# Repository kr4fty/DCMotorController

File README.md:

# DCMotorController

Control de lazo cerrado para motores DC utilizando un ATMEGA328p (corazón del
  Arduino UNO) y un puente H tipo L293.

<!-- TOC depthFrom:1 depthTo:6 withLinks:1 updateOnSave:1 orderedList:0 -->

- [DCMotorController](#dcmotorcontroller)
	- [Descripción](#descripcin)
	- [Funcionamiento](#funcionamiento)
		- [Parámetros PID](#parmetros-pid)
	- [Características:](#caractersticas)
	- [Firmware](#firmware)
		- [Dependencias](#dependencias)
	- [Hardware](#hardware)
		- [Esquematico](#esquematico)
	- [Video](#video)
	- [Motores de corriente continua](#motores-de-corriente-continua)
		- [Ventajas de los Motores DC frente a los PaP](#ventajas-de-los-motores-dc-frente-a-los-pap)
		- [Desventajas de los Motores DC frente a los PaP](#desventajas-de-los-motores-dc-frente-a-los-pap)
	- [Proyectos Similares](#proyectos-similares)
	- [Licencia](#licencia)
	- [Autor](#autor)

<!-- /TOC -->

## Descripción
Este es una pequeña implementación de la librería [ArduinoPID](https://github.com/br3ttb/Arduino-PID-Library), para el control
de motores de corriente continua, DC, que cuenten con un encoder acoplado a su
eje.

Cuenta con soporte para **uno** o **dos** motores, dependiendo de como este
configurado dentro de _**motor.h**_.

La idea principal del proyecto es la de utilizar MOTORES DC/Servos en proyectos
de construcción de CNC en lugar de los tradicionales Motores Paso a Paso (PaP).

El sistema es compatible a nivel de pins de control, con los driver para motores
PaP, **STEP** y **DIR**, como por ejemplo el [Pololu A4988](https://www.pololu.com/product/1182).

## Funcionamiento
Un Arduino cargado con **GRBL**, por ejemplo, envía un pulso a través del pin **STEP**. Cada pulso que recibe el driver le dice al motor que tiene que avanzar un micropaso.

Luego por medio del pin **DIR** obtenemos la dirección de avance, si queremos ir en el sentido de las agujas del reloj, o al contrario.

De esta forma, cada vez que el driver recibe un pulso en el pin **STEP**, el circuito comprueba el estado del pin **DIR**, y alimenta las bobinas del motor en el orden adecuado.

### Parámetros PID
El proceso de sintonizado del PID se hizo de forma experimental, prueba/error, tratando de tener tanto el **overshoot** como el **tiempo de establecimiento** los mas chicos posibles.
Se llego a la conclusión que para el par de motores utilizados, los parámetros que mejor se ajustaban fueron los siguientes:

  * Setpoint > 50: </br>
      Kp = 10 // Agresive Kp</br>
      Ki = 1 // Agresive Ki</br>
      Kd = 0.01 // Agresive Kd</br>

  * Setpoint =< 50:</br>
      Kp = 5  // Conservative Kp</br>
      Ki = 0.1  // Conservative Ki</br>
      Kd = 0.001  // Conservative Kd</br>

Dependiendo del tipo de Motor/Servo utilizados, estos parámetros deberán ser cambiados. Esto ultimo se realizara modificando los prarametros AGGKp,AGGKi, AGGKd, CONSKp, CONSKi y CONSKd, dentro de **motor.h**

## Características:
  * El conjunto Driver-Servo/Motor remplaza al conjunto Driver-Motor/PaP
  * El corazón del sistema es un chip **ATMEGA328p**
  * Se puede controlar uno o dos motores simultáneamente
  * El Driver tiene cuatro señales de control: **DIR**, **STEP**, **ENABLE** y **RESET**
  * Cada motor puede ser controlado de forma independiente por medio de **DIR** y
    **STEP**
  * El sistema de control esta basado en un sistema PID
  * El PWM trabaja a una frecuencia de 31.25KHz, imperceptible al oído humano
  * Cuenta con un salida por puerto serie para depuración
  * Tanto las señales de entrada de los STEPs como las de los encoders, utilizan
    interrupciones del tipo **PIN CHANGE** (PCI)
  * El diseño del **PCB** fue realizado en [KiCAD](https://github.com/KiCad/)
  * La etapa de potencia de los motores fue realizada con un **puente H** del tipo L293D

## Firmware
### Dependencias
El proyecto depende de cuatro librerías:
  * [ArduinoPID](https://github.com/br3ttb/Arduino-PID-Library): Librería principal con la que se realiza el control de lazo
    cerrado
  * [EnableInterrupt](https://github.com/GreyGnome/EnableInterrupt): Encargada de vincular las interrupciones del tipo Pin-change con la respectiva ISR.
  * [EncoderPCI](https://github.com/kr4fty/EncoderPCI): Librería encargada de manejar los Encoders
  * [DCMotorServoPCI](https://github.com/kr4fty/DCMotorServoPCI): Es la librería en si, que realiza la gestión y el control del
    motor dc

## Hardware
Pins utilizados:

<table>
	<tr><th></th><th> Motor 1 </th></tr>
	<tr><th> <b>Arduino Pin</b> </th><th> <b>Descripción</b> </th></tr>
	<tr><td>10 </td><td> pwmX, chip enable 1 del L293D </td></tr>
	<tr><td>6  </td><td> in1X, salida hacia el pin 2, IN1, del L293D </td></tr>
	<tr><td>5  </td><td> in2X, salida hacia el pin 7, IN2, del L293D </td></tr>
	<tr><td>A2 </td><td> inAX, entrada A desde el encoder </td></tr>
	<tr><td>A3 </td><td> inBX, entrada B desde el encoder </td></tr>
	<tr><td>2  </td><td> stepX, entrada STEP proveniente del otro Arduino cargado con GRBL </td></tr>
	<tr><td>12 </td><td> dirX, entrada DIR proveniente del otro Arduino cargado con GRBL </td></tr>
</table>

<table>
	<tr><th></th><th> Motor 2 </th></tr>
	<tr><th> <b>Arduino Pin</b> </th><th> <b>Descripción</b> </th></tr>
	<tr><td> 11 </td><td> pwmY, chip enable 2 del L293D </td></tr>
	<tr><td> 8 </td><td> in1Y, salida hacia el pin 10, IN3, del L293D </td></tr>
	<tr><td> 9 </td><td> in2Y, salida hacia el pin 15, IN4, del L293D </td></tr>
	<tr><td> A0 </td><td> inAY, entrada A desde el encoder </td></tr>
	<tr><td> A1 </td><td> inBY, entrada B desde el encoder </td></tr>
	<tr><td> 3 </td><td> stepY, entrada STEP </td></tr>
	<tr><td> 13 </td><td> dirY, entrada DIR </td></tr>
</table>

<table>
	<tr><th></th><th> Global </th></tr>
	<tr><th> <b>Arduino Pin</b> </th><th> <b>Descripción</b> </th></tr>
	<tr><td> A5 </td><td> entrada ENABLE </td></tr>
	<tr><td> Rst </td><td> Reset del driver </td></tr>
</table>

### Esquematico

<p align="center">
  <br><br>
  <b>Circuito</b><br>
  
  <br>
</p>

## Video
<p align="center">
  <b>YouTube</b><br>
  
</p>

## Motores de corriente continua

### Ventajas de los Motores DC frente a los PaP
  * Poseen gran velocidad de giro
  * Alta aceleración/Par inicial
  * Son silenciosos
  * Movimiento suave y sin saltos
  * Control medianamente sencilla
  * Electrónica mas sencilla
  * Utiliza realimentación para el control del sistema
  * Debido a este ultimo, tiene alta precisión en posición (depende fuertemente
    del encoder acoplado)

### Desventajas de los Motores DC frente a los PaP
  * La potencia de funcionamiento pico sólo se desarrolla a altas velocidades
  * Debido a sus altas velocidades estos pueden calentarse mas rápidamente
    (podría necesitar un sistemas de ventilación)
  * Inercia mas elevada (depende de la  velocidad y la carga acoplada al eje)

## Proyectos Similares
  * [ServoStrap](https://github.com/danithebest91/ServoStrap) por _danithebest91_
  * [SuryaProCell-CNC](https://github.com/suryaprocell/SuryaProCell-CNC) por _suryaprocell_
  * [DC-Servo-Controller](https://github.com/makerbot/DC-Servo-Controller) por _makerbot_
  * [dcservo](https://github.com/misan/dcservo) por _misan_

## Licencia

GPLv2

## Autor

Tapia Favio

## Feedback

Por favor agradecería que me envies cualquier duda y/o comentario para mejorar el proyecto, gracias.

Mail: technicc (at) gmail.com

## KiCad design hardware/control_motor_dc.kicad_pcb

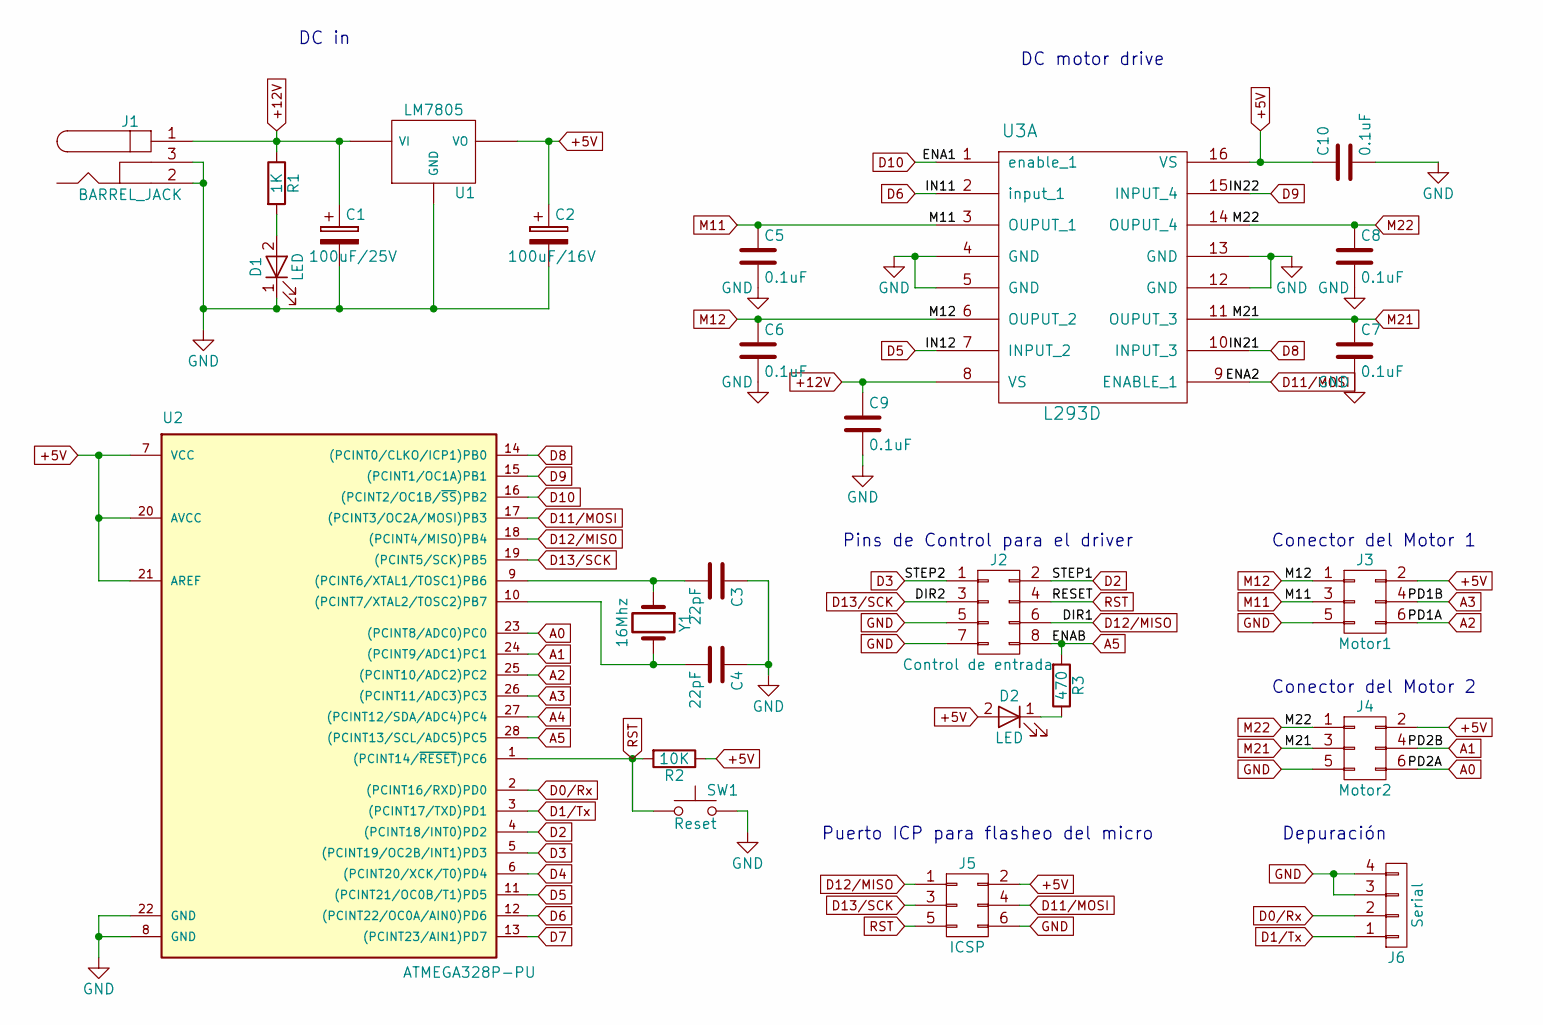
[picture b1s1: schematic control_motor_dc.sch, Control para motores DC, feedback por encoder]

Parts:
C1: 100uF/25V; CP_Radial_D5.0mm_P2.50mm
C2: 100uF/16V; CP_Radial_D5.0mm_P2.00mm
C3, C4: 22pF; C_Disc_D3.8mm_W2.6mm_P2.50mm
C5, C6, C7, C8, C9, C10: 0.1uF; C_Disc_D3.8mm_W2.6mm_P2.50mm
D1, D2: LED; LED_D3.0mm
J1: BARREL_JACK; JACK_ALIM
J2: Control de entrada; Socket_Strip_Straight_2x04_Pitch2.54mm
J3: Motor1; Socket_Strip_Straight_2x03_Pitch2.54mm
J4: Motor2; Socket_Strip_Straight_2x03_Pitch2.54mm
J5: ICSP; Pin_Header_Straight_2x03_Pitch2.54mm
J6: Serial; Pin_Header_Straight_1x04_Pitch2.54mm
R1: 1K; R_Axial_DIN0207_L6.3mm_D2.5mm_P2.54mm_Vertical
R2: 10K; R_Axial_DIN0207_L6.3mm_D2.5mm_P7.62mm_Horizontal
R3: 470; R_Axial_DIN0204_L3.6mm_D1.6mm_P7.62mm_Horizontal
SW1: Reset; SW_PUSH_6mm
U1: LM7805; TO-220_Vertical-fav
U2: ATMEGA328P-PU; DIP-28_W7.62mm
U3: L293D; DIP-16_W7.62mm
Y1: 16Mhz; Crystal_HC52-6mm_Vertical

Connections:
+5V: C2.1, C10.1, D2.2 (A), J3.2, J4.2, J5.2, R2.1, U1.VO, U2.7 (VCC), U2.20 (AVCC), U2.21 (AREF), U3.16 (VS)
+12V: C1.1, C9.1, J1.1, R1.1, U1.VI, U3.8 (VS)
A0: J4.6, U2.23 ((PCINT8/ADC0)PC0)
A1: J4.4, U2.24 ((PCINT9/ADC1)PC1)
A2: J3.6, U2.25 ((PCINT10/ADC2)PC2)
A3: J3.4, U2.26 ((PCINT11/ADC3)PC3)
A4: U2.27 ((PCINT12/SDA/ADC4)PC4)
A5: J2.8, R3.2, U2.28 ((PCINT13/SCL/ADC5)PC5)
D0/Rx: J6.2, U2.2 ((PCINT16/RXD)PD0)
D1/Tx: J6.1, U2.3 ((PCINT17/TXD)PD1)
D2: J2.2, U2.4 ((PCINT18/INT0)PD2)
D3: J2.1, U2.5 ((PCINT19/OC2B/INT1)PD3)
D4: U2.6 ((PCINT20/XCK/T0)PD4)
D5: U2.11 ((PCINT21/OC0B/T1)PD5), U3.7 (INPUT_2)
D6: U2.12 ((PCINT22/OC0A/AIN0)PD6), U3.2 (input_1)
D7: U2.13 ((PCINT23/AIN1)PD7)
D8: U2.14 ((PCINT0/CLKO/ICP1)PB0), U3.10 (INPUT_3)
D9: U2.15 ((PCINT1/OC1A)PB1), U3.15 (INPUT_4)
D10: U2.16 ((PCINT2/OC1B/~SS~)PB2), U3.1 (enable_1)
D11/MOSI: J5.4, U2.17 ((PCINT3/OC2A/MOSI)PB3), U3.9 (ENABLE_1)
D12/MISO: J2.6, J5.1, U2.18 ((PCINT4/MISO)PB4)
D13/SCK: J2.3, J5.3, U2.19 ((PCINT5/SCK)PB5)
GND: C1.2, C2.2, C3.1, C4.1, C5.2, C6.2, C7.2, C8.2, C9.2, C10.2, D1.1 (K), J1.2, J1.3, J2.5, J2.7, J3.5, J4.5, J5.6, J6.3, J6.4, SW1.2, U1.GND, U2.8 (GND), U2.22 (GND), U3.4 (GND), U3.5 (GND), U3.12 (GND), U3.13 (GND)
M11: C5.1, J3.3, U3.3 (OUPUT_1)
M12: C6.1, J3.1, U3.6 (OUPUT_2)
M21: C7.1, J4.3, U3.11 (OUPUT_3)
M22: C8.1, J4.1, U3.14 (OUPUT_4)
unnamed: C3.2, U2.9 ((PCINT6/XTAL1/TOSC1)PB6), Y1.1
unnamed: C4.2, U2.10 ((PCINT7/XTAL2/TOSC2)PB7), Y1.2
unnamed: D1.2 (A), R1.2
unnamed: D2.1 (K), R3.1
RST: J2.4, J5.5, R2.2, SW1.1, U2.1 ((PCINT14/~RESET~)PC6)

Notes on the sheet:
DC motor drive
Pins de Control para el driver
Puerto ICP para flasheo del micro
Conector del Motor 1
Conector del Motor 2
Depuración
DC in

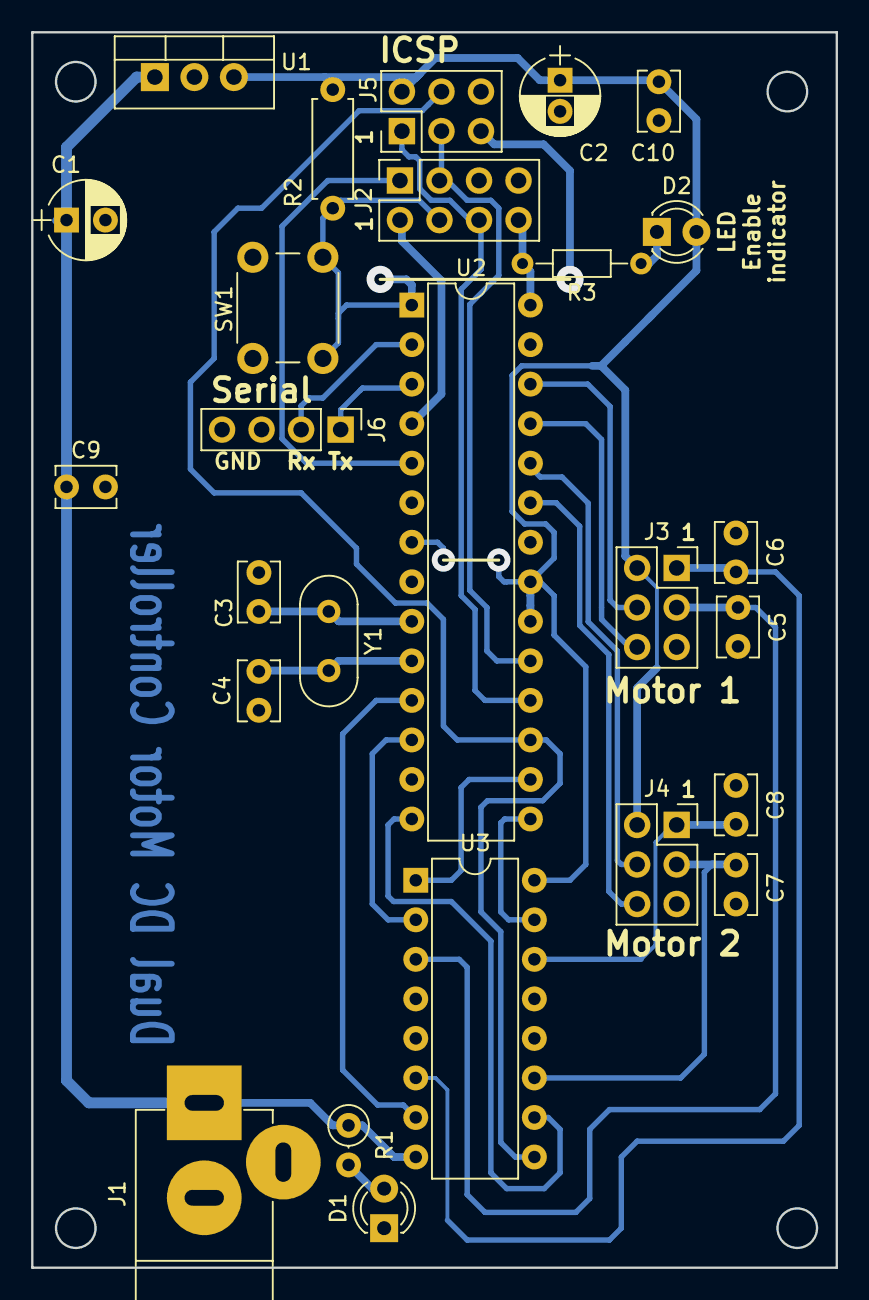
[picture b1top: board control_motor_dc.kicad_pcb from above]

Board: 2 copper layers, 51.7 x 79.4 mm, 26 parts (0 on the bottom side), 29 nets.

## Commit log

2017-07-15 update lib
2017-11-13 feedback
2017-11-13 edit motor.h
